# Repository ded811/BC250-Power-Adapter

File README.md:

# BC-250 J2000/J2001 Power Adapter

> ## ⚠️ UNTESTED
> **I'm still waiting on my boards from fab. This design has not been built or tested on real hardware yet.** Posting early since others were interested. Build at your own risk until this notice is removed.

A simple PCB that adapts the BC-250's J2000 and J2001 power ports to standard PSU cables. One side has two Micro-Fit connectors that plug into the board, the other side has a PCIe 8-pin (GPU cable) and an EPS 8-pin (CPU cable) header for your PSU cables. No components, just copper connecting one side to the other.

KiCad project files are in this repo.

---

## ⚠️ Warnings

- **Use a single-rail PSU (or one with bridged rails) if you power the board from more than one connector.** That means both headers on this adapter, or this adapter plus the board's own GPU connector (J1000). Two independent rails tied together will trip over-current protection at best, damage the PSU at worst. Multi-rail server and mining PSUs are the usual culprits.

---

## Parts

Pick one option. Both include the two Micro-Fit connectors for the BC-250 side.

### Option 1: Keyed (preferred)

| Qty | Part | Function | Price | Source |
|---|---|---|---|---|
| 2 | Molex **0447690801**, 8-pos Micro-Fit 3.0 BMI receptacle | Plugs into J2000 / J2001 | $4.75 ea ($9.50) | [DigiKey](https://www.digikey.com/en/products/detail/molex/0447690801/513218) |
| 1 | 8-pin PCIe male header, 90°, keyed | Takes a GPU cable | $1.99 | [ModDIY](https://www.moddiy.com/products/2427/8-Pin-Graphics-Card-PCIe-Male-Header-Connector-90-Degree-Angled-Black.html) |
| 1 | 8-pin EPS male header, 90°, keyed | Takes a CPU cable | $1.99 | [ModDIY](https://www.moddiy.com/products/4298/8-Pin-CPU-EPS-Male-Header-Connector-90-Degree-Angled-Black.html) |

Parts: $13.48 + shipping from both DigiKey ($4.99) and ModDIY ($9.99) = **~$28.50 total**

Keyed connectors physically block the wrong cable type. Molex doesn't sell these to individuals, so buy them from a trusted reseller like ModDIY.

### Option 2: Single DigiKey order (cheaper, some caveats)

| Qty | Part | Function | Price | Source |
|---|---|---|---|---|
| 2 | Molex **0447690801**, 8-pos Micro-Fit 3.0 BMI receptacle | Plugs into J2000 / J2001 | $4.75 ea ($9.50) | [DigiKey](https://www.digikey.com/en/products/detail/molex/0447690801/513218) |
| 2 | Molex **0039301080**, Mini-Fit Jr 8-pos male header, 90° | CPU header (see note for GPU) | $0.85 ea ($1.70) | [DigiKey](https://www.digikey.com/en/products/detail/molex/0039301080/561081) |

Parts: $11.20 + DigiKey shipping ($4.99) = **~$16.20 total**

**Heads up: the 0039301080 only accepts a CPU (EPS) cable as-is.** Its keying matches EPS housings, but GPU cables have a different key pattern (a plastic bridge between the pin rows) and won't seat. Tested and confirmed. For the GPU header you have three choices:

1. **Buy the ModDIY PCIe header** from Option 1 for that position (adds ModDIY shipping, so most of the savings disappear)
2. **Trim the keying** off a 0039301080 with a hobby knife. The shroud is nylon and cuts easily; take off less than you think, test-fit as you go, and don't nick the pins or the latch wall. A trimmed header accepts **both** cable types, so the warning below applies in full. Do this at your own risk.
3. **AliExpress GPU headers** [like these](https://www.aliexpress.us/item/2255799861263552.html) exist and can work, but aren't recommended (unknown terminal quality on a high-current part). If you go this route anyway, get the **GPU-8Pin-RA** variant, **NOT the GPU-8Pin-RA-Reversed** one.

> **⚠️ Never plug a CPU cable into the GPU header or the other way around.** PCIe and EPS pinouts are mirrored, so the wrong cable puts 12V where ground should be. This can kill the board and the PSU. The keyed connectors in Option 1 physically block the wrong cable. A trimmed header blocks nothing, so label your headers and double check before powering on.

---

## Pinout (BC-250 side)

From `mothenjoyer69/bc250-documentation`:

```
        J2000                    J2001
     v                        v
[ LED1  12V   12V   12V ]  [ 12V   12V   12V   GND ]
[ LED2  GND   GND   GND ]  [ GND   GND   GND   PGD ]
```

| Pin | Function |
|---|---|
| LED1 | Active-low output, mirrors the rack's green backplane LED |
| LED2 | Active-low output, mirrors the rack's red backplane LED |
| PGD | Power-good signal, reads 5V when a second PSU is on the rack's distribution board |

LED1 and LED2 are broken out as labeled headers on this adapter. They're logic outputs, not a power source. To add a status LED, wire it from the pin to 12V through a resistor, cathode toward the pin. Drive strength isn't documented, so size the resistor conservatively.

---

## Power

**BC-250 side:** Micro-Fit contacts are rated 5A each. Three 12V pins per connector gives 6 x 5A x 12V = **360W** across both.

**PSU side:**

| Header | Safe continuous | Theoretical max |
|---|---|---|
| PCIe 8-pin | ~150W | ~324W |
| EPS 8-pin | ~235W | ~432W |

Plan around the safe numbers. The max figures are raw pin ratings with zero margin.

**Check your cable gauge.** The ratings above assume decent wire. 16 AWG handles the full connector rating, 18 AWG has melted on this board under sustained load, and 20 AWG (common on cheap or SFF cables) is only good for roughly half the rated current per wire. This adapter exists partly for that reason: splitting the load across both a GPU and a CPU cable keeps the current per wire low enough that even thin cables stay safe.

**What the BC-250 actually draws:**

| Scenario | Draw |
|---|---|
| Idle | ~70-95W |
| Stock 24 CU gaming | ~150-200W, peaks near 250W |
| 40 CU @ 1500 MHz | ~125-150W |
| 40 CU @ 2 GHz | ~181W GPU alone, more with CPU load |
| Sustained full load | Can pass 320W |

One EPS header alone is tight even at stock, since gaming can peak past its 235W rating. **Use both headers for anything overclocked or under sustained load.** Together they're good for ~385W, which covers everything the board can realistically pull.

PSU sizing from the community: 250W+ on the 12V rail before overclocking, 300W+ for heavy overclocks, 400-500W+ for sustained full-CU compute.

---

## Disclaimer

Based on community reverse engineering, not official schematics. Verify pinouts against your own board before applying power. Use at your own risk.

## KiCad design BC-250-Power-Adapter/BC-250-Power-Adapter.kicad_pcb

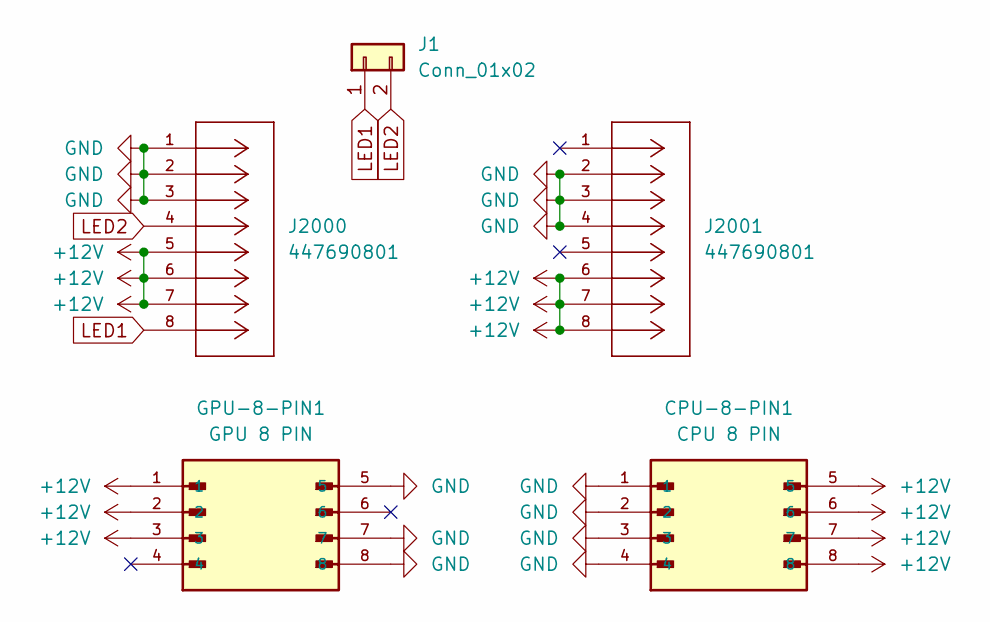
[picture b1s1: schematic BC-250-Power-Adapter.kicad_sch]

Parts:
CPU-8-PIN1: CPU 8 PIN; MOLEX_39301081; PARTREV A
GPU-8-PIN1: GPU 8 PIN; MOLEX_39301081; PARTREV A
J1: Conn_01x02; PinHeader_1x02_P2.54mm_Vertical
J2000, J2001: 447690801; CONN_SD-44769-001_08_MOL; MANUFACTURER_PART_NUMBER 447690801

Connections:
+12V: CPU-8-PIN1.5, CPU-8-PIN1.6, CPU-8-PIN1.7, CPU-8-PIN1.8, GPU-8-PIN1.1, GPU-8-PIN1.2, GPU-8-PIN1.3, J2000.5, J2000.6, J2000.7, J2001.6, J2001.7, J2001.8
GND: CPU-8-PIN1.1, CPU-8-PIN1.2, CPU-8-PIN1.3, CPU-8-PIN1.4, GPU-8-PIN1.5, GPU-8-PIN1.7, GPU-8-PIN1.8, J2000.1, J2000.2, J2000.3, J2001.2, J2001.3, J2001.4
LED1: J1.1, J2000.8
LED2: J1.2, J2000.4

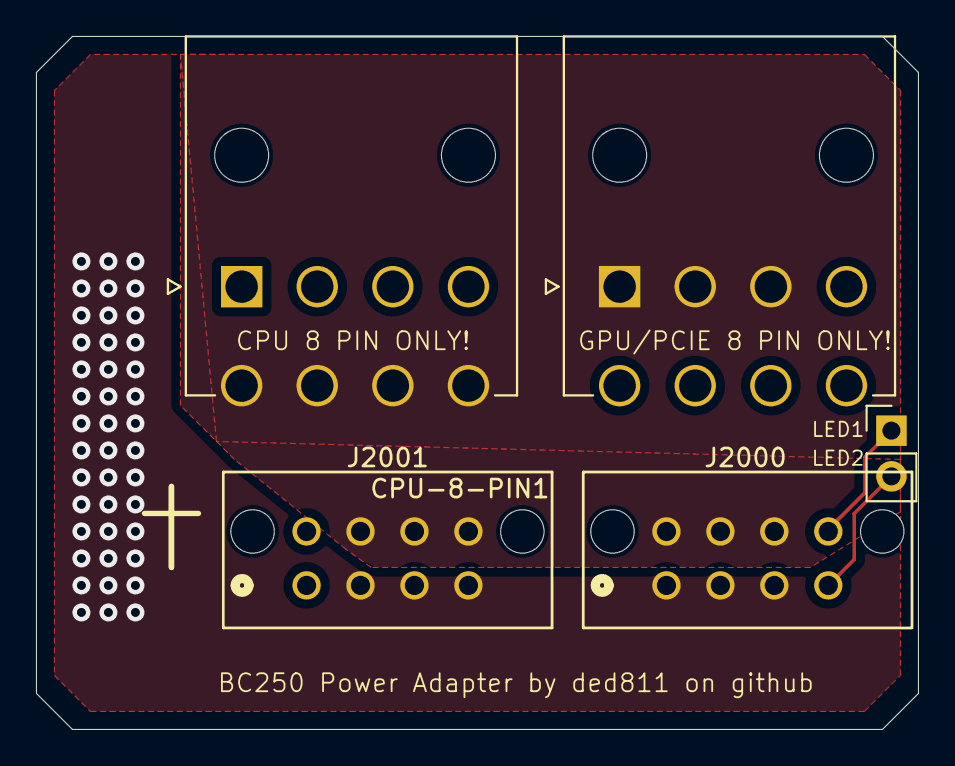
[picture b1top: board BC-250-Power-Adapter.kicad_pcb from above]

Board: 2 copper layers, 49.0 x 38.5 mm, 5 parts (0 on the bottom side), 4 nets.

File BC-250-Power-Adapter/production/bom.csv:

Designator,Footprint,Quantity,Value,LCSC Part #
CPU-8-PIN1,MOLEX_39301081,1,CPU 8 PIN,
GPU-8-PIN1,MOLEX_39301081,1,GPU 8 PIN,
J1,PinHeader_1x02_P2.54mm_Vertical,1,Conn_01x02,
"J2000, J2001",CONN_SD-44769-001_08_MOL,2,447690801,
